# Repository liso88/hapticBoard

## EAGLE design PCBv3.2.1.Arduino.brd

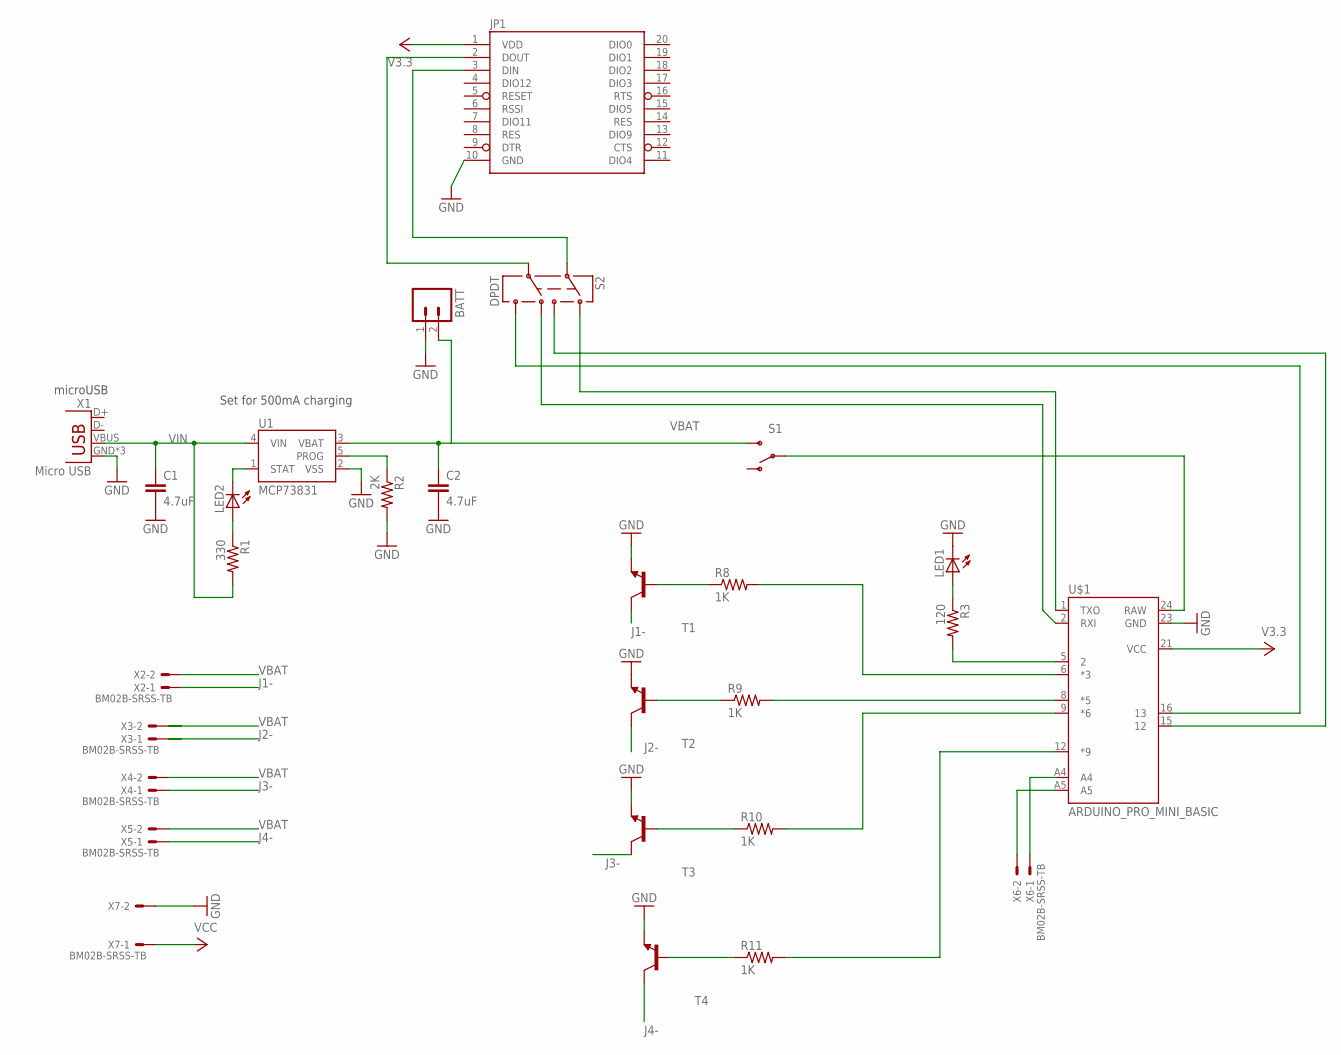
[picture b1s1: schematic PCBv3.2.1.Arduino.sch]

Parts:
BATT: M02JST-PTH-VERT; JST-2-PTH-VERT; MPN S2B-PH-K-S (LF)(SN)
C1, C2: 4.7uF; C0805; MPN C1005X5R0J475K050BC
JP1: XBEE-1LONGPAD; XBEE-LONGPAD
LED1: LED3MM; MPN MCL034GT
LED2: LEDCHIP-LED0805; CHIP-LED0805; MPN KPT-2012QBC-D
R1: 330; R0805; MPN MC01W08051330R
R2: 2K; R0805; MPN MC01W080512K
R3: 120; R0805; MPN ASMT-YWB1-NGJB2
R8, R9, R10, R11: 1K; R0805; MPN MC01W08051330R
S1: SWITCH-SPDTPTH; SWITCH-SPDT; MPN 09-10201-02
S2: DPDT; AYZ0202; MPN AYZ0202AGRLC
T1, T2, T3, T4: BC817-16-NPN-SOT23-BEC; SOT23-BEC; MPN BC817-40LT3G
U1: MCP73831; SOT23-5; MPN MCP73831T-2ACI/OT
U$1: ARDUINO_PRO_MINI_BASIC
X1: Micro USB; USB-MICROB; MPN ZX62-B-5PA(33)
X2, X3, X4, X5, X6, X7: BM02B-SRSS-TB

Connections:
GND: BATT.1, C1.2, C2.2, JP1.10 (GND), LED1.K (C), R2.2, T1.E, T2.E, T3.E, T4.E, U1.2 (VSS), U$1.23 (GND), X1.GND, X1.MT1 (GND), X1.MT2 (GND), X7.2
J1-: T1.C, X2.1
J2-: T2.C, X3.1
J3-: T3.C, X4.1
J4-: T4.C, X5.1
unnamed: R3.2, U$1.5 (2)
unnamed: U$1.A4, X6.1
unnamed: U$1.A5, X6.2
unnamed: R10.2, U$1.9 (*6)
unnamed: S2.1 (3), U$1.15 (12)
unnamed: S1.2, U$1.24 (RAW)
unnamed: LED1.A, R3.1
unnamed: R9.2, U$1.8 (*5)
unnamed: R8.1, T1.B
unnamed: R8.2, U$1.6 (*3)
unnamed: LED2.A, R1.1
unnamed: S2.4 (6), U$1.16 (13)
unnamed: R9.1, T2.B
unnamed: R11.1, T4.B
unnamed: S2.6 (4), U$1.2 (RXI)
unnamed: S2.3 (1), U$1.1 (TXO)
unnamed: R11.2, U$1.12 (*9)
unnamed: R10.1, T3.B
unnamed: JP1.2 (DOUT), S2.5
unnamed: JP1.3 (DIN), S2.2
PROG: R2.1, U1.5 (PROG)
STAT: LED2.C, U1.1 (STAT)
VBAT: BATT.2, C2.1, S1.3 (S), U1.3 (VBAT), X2.2, X3.2, X4.2, X5.2
VCC: JP1.1 (VDD), U$1.21 (VCC), X7.1
VIN: C1.1, R1.2, U1.4 (VIN), X1.VBUS

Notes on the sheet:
Set for 500mA charging
microUSB

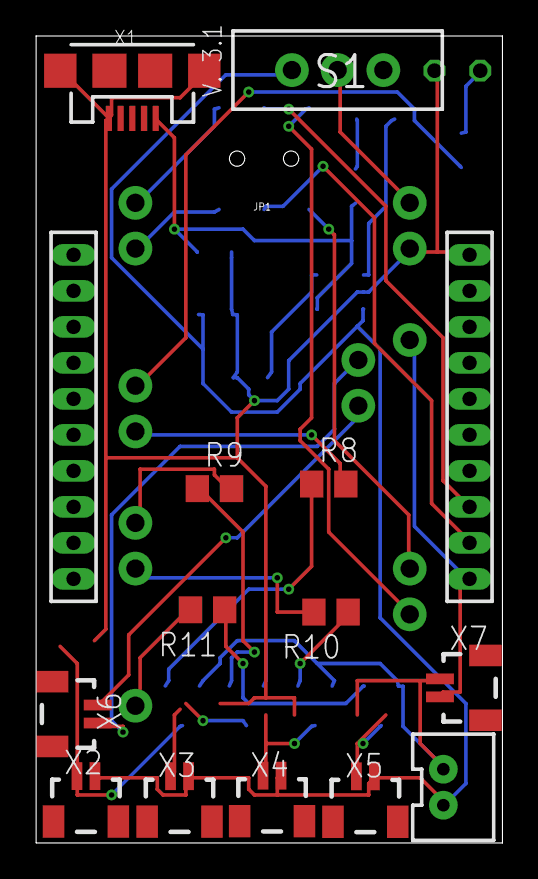
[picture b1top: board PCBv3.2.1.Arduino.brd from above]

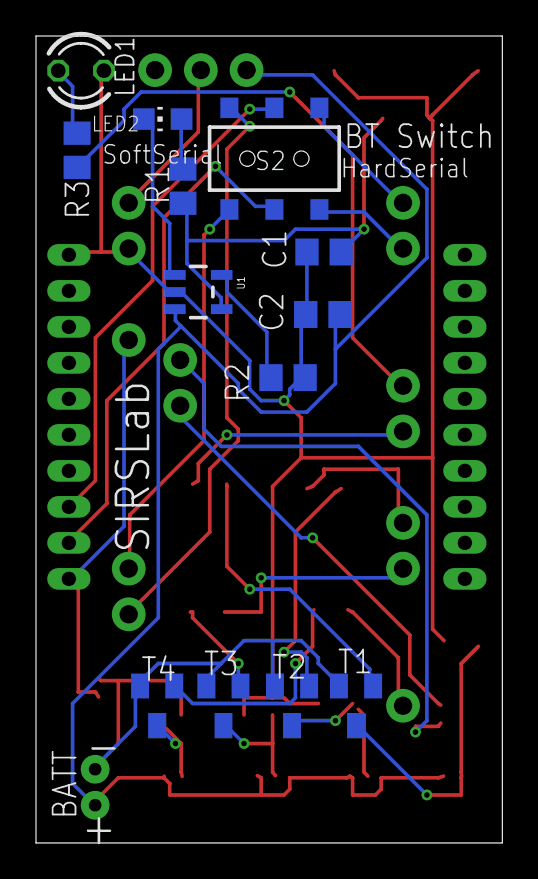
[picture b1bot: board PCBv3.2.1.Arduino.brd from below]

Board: 2 copper layers, 25.9 x 44.8 mm, 28 parts (13 on the bottom side), 30 nets.

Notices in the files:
parts and their libraries:
SparkFun-RF: Licensing: Creative Commons ShareAlike 4.0 International - https://creativecommons.org/licenses/by-sa/4.0
SparkFun-Electromechanical: Licensing: CC v3.0 Share-Alike You are welcome to use this library for commercial purposes.
